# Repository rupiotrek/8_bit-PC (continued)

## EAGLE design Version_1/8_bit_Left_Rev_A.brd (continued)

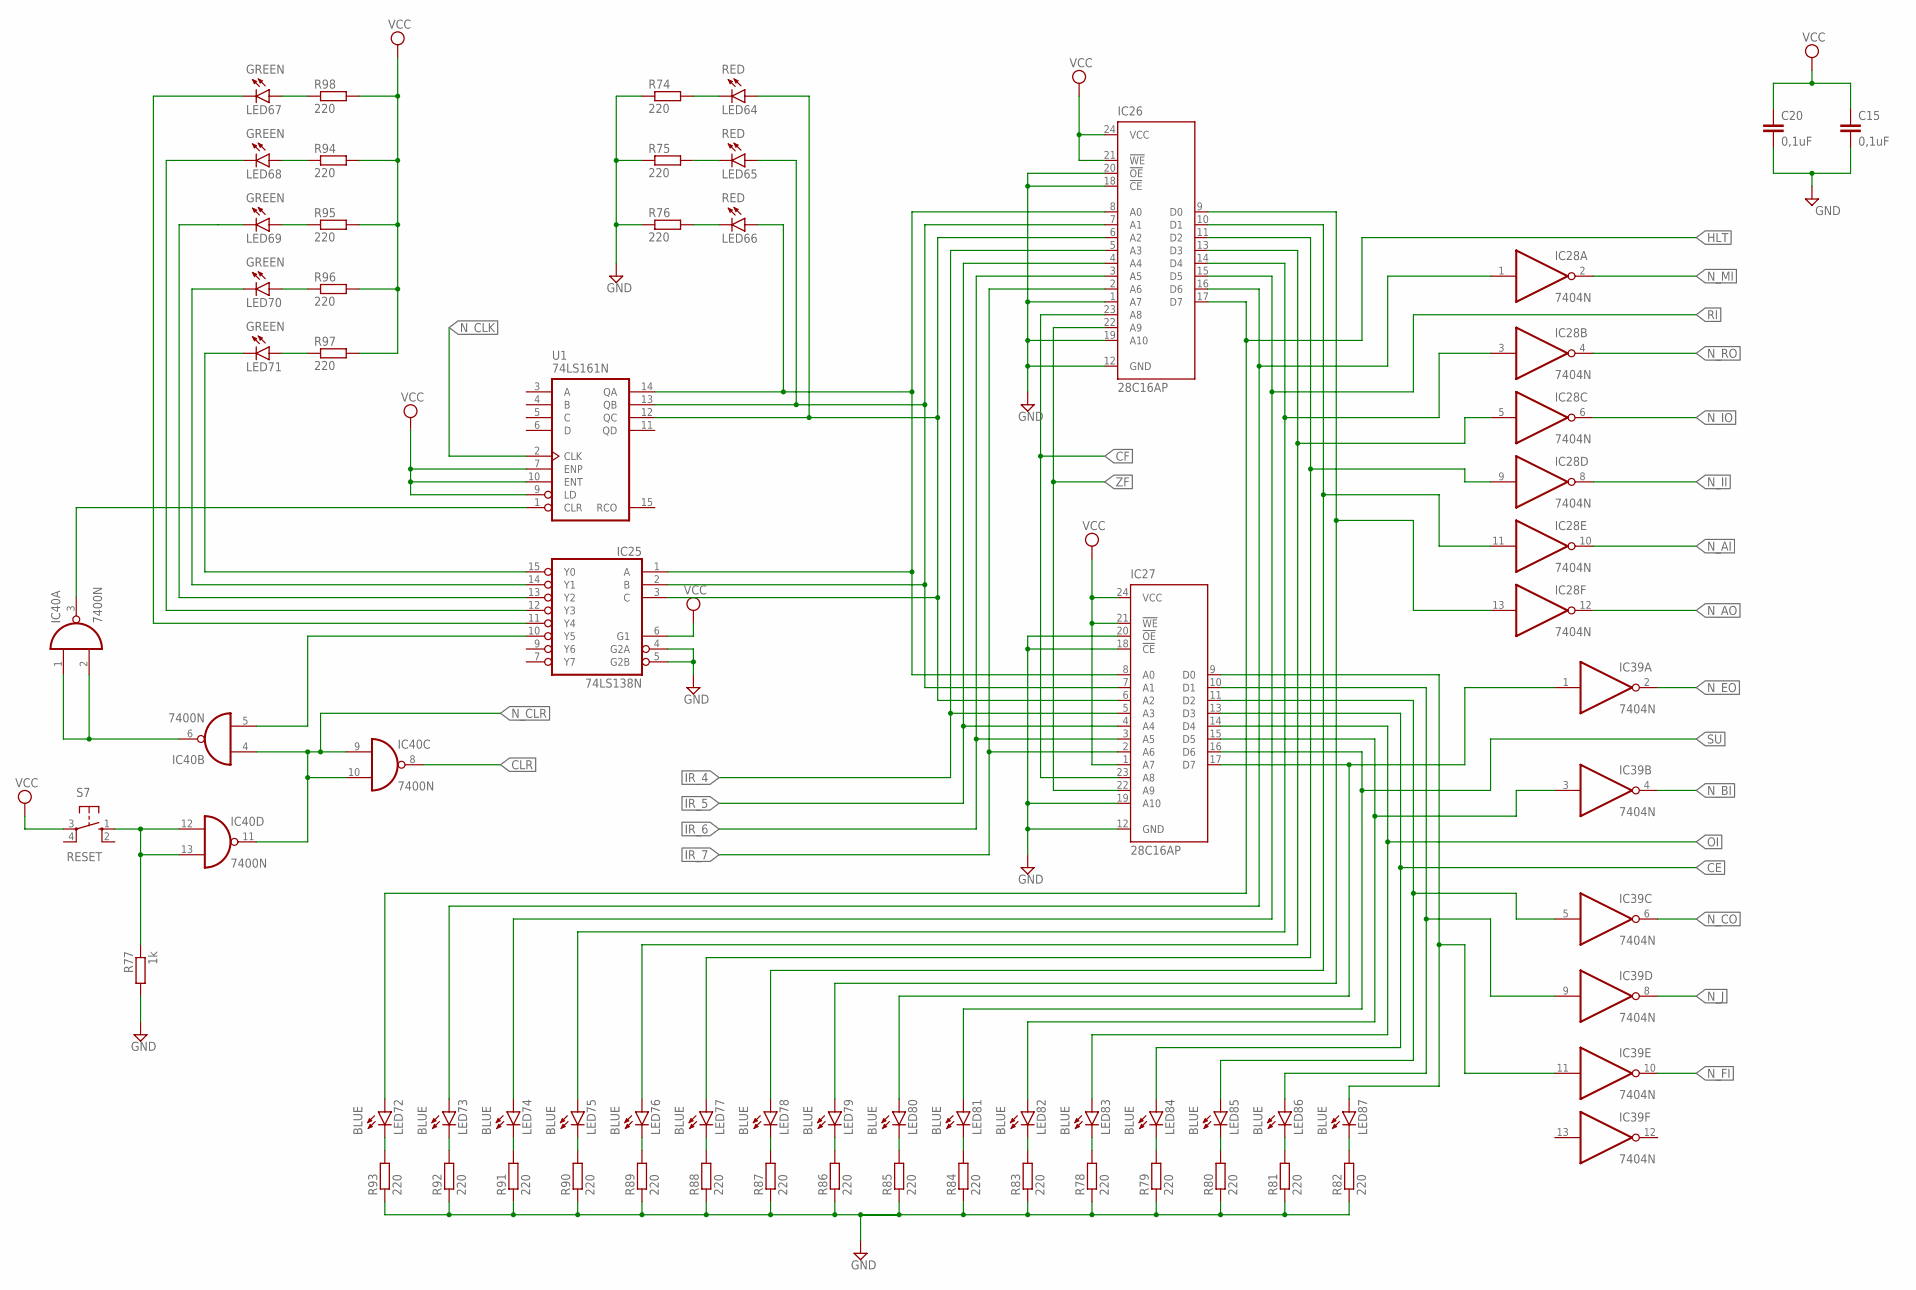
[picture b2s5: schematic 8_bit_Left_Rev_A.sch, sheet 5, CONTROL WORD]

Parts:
C15, C20: 0,1uF; C025-030X050
IC25: 74LS138N; DIL16
IC26, IC27: 28C16AP; DIL24-6
IC28, IC39: 7404N; DIL14
IC40: 7400N; DIL14
LED64, LED65, LED66: RED; LED5MM
LED67, LED68, LED69, LED70, LED71: GREEN; LED5MM
LED72, LED73, LED74, LED75, LED76, LED77, LED78, LED79, LED80, LED81, LED82, LED83, LED84, LED85, LED86, LED87: BLUE; LED5MM
R74, R75, R76, R78, R79, R80, R81, R82, R83, R84, R85, R86, R87, R88, R89, R90, R91, R92, R93, R94, R95, R96, R97, R98: 220; 0207/10
R77: 1k; 0207/10
S7: RESET; B3F-10XX
U1: 74LS161N; DIL16

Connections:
ASD1: IC25.10 (Y5), IC40.5 (I1)
CE: IC27.13 (D3), LED84.A; also elsewhere on the board
CF: IC26.23 (A8), IC27.23 (A8); also elsewhere on the board
CLK4: IC25.1 (A), IC26.8 (A0), IC27.8 (A0), LED66.A, U1.14 (QA)
CLK5: IC25.2 (B), IC26.7 (A1), IC27.7 (A1), LED65.A, U1.13 (QB)
CLK6: IC25.3 (C), IC26.6 (A2), IC27.6 (A2), LED64.A, U1.12 (QC)
CLR: IC40.8 (O); also elsewhere on the board
GND: C15.2, C20.2, IC25.4 (G2A), IC25.5 (G2B), IC25.8 (GND), IC26.1 (A7), IC26.12 (GND), IC26.18 (!CE), IC26.19 (A10), IC26.20 (!OE), IC27.12 (GND), IC27.18 (!CE), IC27.19 (A10), IC27.20 (!OE), IC28.7 (GND), IC39.7 (GND), IC40.7 (GND), R74.1, R75.1, R76.1, R77.2, R78.1, R79.1, R80.1, R81.1, R82.1, R83.1, R84.1, R85.1, R86.1, R87.1, R88.1, R89.1, R90.1, R91.1, R92.1, R93.1, U1.8 (GND); also elsewhere on the board
GND61: LED64.K (C), R74.2
GND62: LED65.K (C), R75.2
GND63: LED66.K (C), R76.2
GND64: IC25.12 (Y3), LED68.K (C)
GND65: IC25.13 (Y2), LED69.K (C)
GND66: IC25.14 (Y1), LED70.K (C)
GND67: IC25.15 (Y0), LED71.K (C)
GND68: IC25.11 (Y4), LED67.K (C)
GND69: LED83.K (C), R78.2
GND70: LED84.K (C), R79.2
GND71: LED85.K (C), R80.2
GND72: LED86.K (C), R81.2
GND73: LED87.K (C), R82.2
GND74: LED82.K (C), R83.2
GND75: LED81.K (C), R84.2
GND76: LED80.K (C), R85.2
GND77: LED79.K (C), R86.2
GND78: LED78.K (C), R87.2
GND79: LED77.K (C), R88.2
GND80: LED76.K (C), R89.2
GND81: LED75.K (C), R90.2
GND82: LED74.K (C), R91.2
GND83: LED73.K (C), R92.2
GND84: LED72.K (C), R93.2
HLT: IC26.17 (D7), LED72.A; also elsewhere on the board
IR_4: IC26.5 (A3), IC27.5 (A3); also elsewhere on the board
IR_5: IC26.4 (A4), IC27.4 (A4); also elsewhere on the board
IR_6: IC26.3 (A5), IC27.3 (A5); also elsewhere on the board
IR_7: IC26.2 (A6), IC27.2 (A6); also elsewhere on the board
unnamed: IC40.1 (I0), IC40.2 (I1), IC40.6 (O)
unnamed: IC40.3 (O), U1.1 (CLR)
unnamed: IC40.12 (I0), IC40.13 (I1), R77.1, S7.1 (S)
unnamed: IC26.14 (D4), IC28.3 (I), LED75.A
unnamed: IC26.13 (D3), IC28.5 (I), LED76.A
unnamed: IC26.11 (D2), IC28.9 (I), LED77.A
unnamed: IC26.10 (D1), IC28.11 (I), LED78.A
unnamed: IC26.9 (D0), IC28.13 (I), LED79.A
unnamed: IC27.17 (D7), IC39.1 (I), LED80.A
unnamed: IC27.15 (D5), IC39.3 (I), LED82.A
unnamed: IC27.11 (D2), IC39.5 (I), LED85.A
unnamed: IC27.10 (D1), IC39.9 (I), LED86.A
unnamed: IC27.9 (D0), IC39.11 (I), LED87.A
unnamed: LED69.A, R95.1
unnamed: LED68.A, R94.1
unnamed: LED70.A, R96.1
unnamed: LED67.A, R98.1
unnamed: LED71.A, R97.1
N_AI: IC28.10 (O); also elsewhere on the board
N_AO: IC28.12 (O); also elsewhere on the board
N_BI: IC39.4 (O); also elsewhere on the board
N_CLK: U1.2 (CLK); also elsewhere on the board
N_CLR: IC40.4 (I0), IC40.9 (I0), IC40.10 (I1), IC40.11 (O); also elsewhere on the board
N_CO: IC39.6 (O); also elsewhere on the board
N_EO: IC39.2 (O); also elsewhere on the board
N_FI: IC39.10 (O); also elsewhere on the board
N_II: IC28.8 (O); also elsewhere on the board
N_IO: IC28.6 (O); also elsewhere on the board
N_J: IC39.8 (O); also elsewhere on the board
N_MI: IC28.2 (O); also elsewhere on the board
N_RO: IC28.4 (O); also elsewhere on the board
OI: IC27.14 (D4), LED83.A; also elsewhere on the board
QWER1: IC26.16 (D6), IC28.1 (I), LED73.A
RI: IC26.15 (D5), LED74.A; also elsewhere on the board
SU: IC27.16 (D6), LED81.A; also elsewhere on the board
VCC: C15.1, C20.1, IC25.6 (G1), IC25.16 (VCC), IC26.21 (!WE), IC26.24 (VCC), IC27.1 (A7), IC27.21 (!WE), IC27.24 (VCC), IC28.14 (VCC), IC39.14 (VCC), IC40.14 (VCC), R94.2, R95.2, R96.2, R97.2, R98.2, S7.3, U1.7 (ENP), U1.9 (LD), U1.10 (ENT), U1.16 (VCC); also elsewhere on the board
ZF: IC26.22 (A9), IC27.22 (A9); also elsewhere on the board

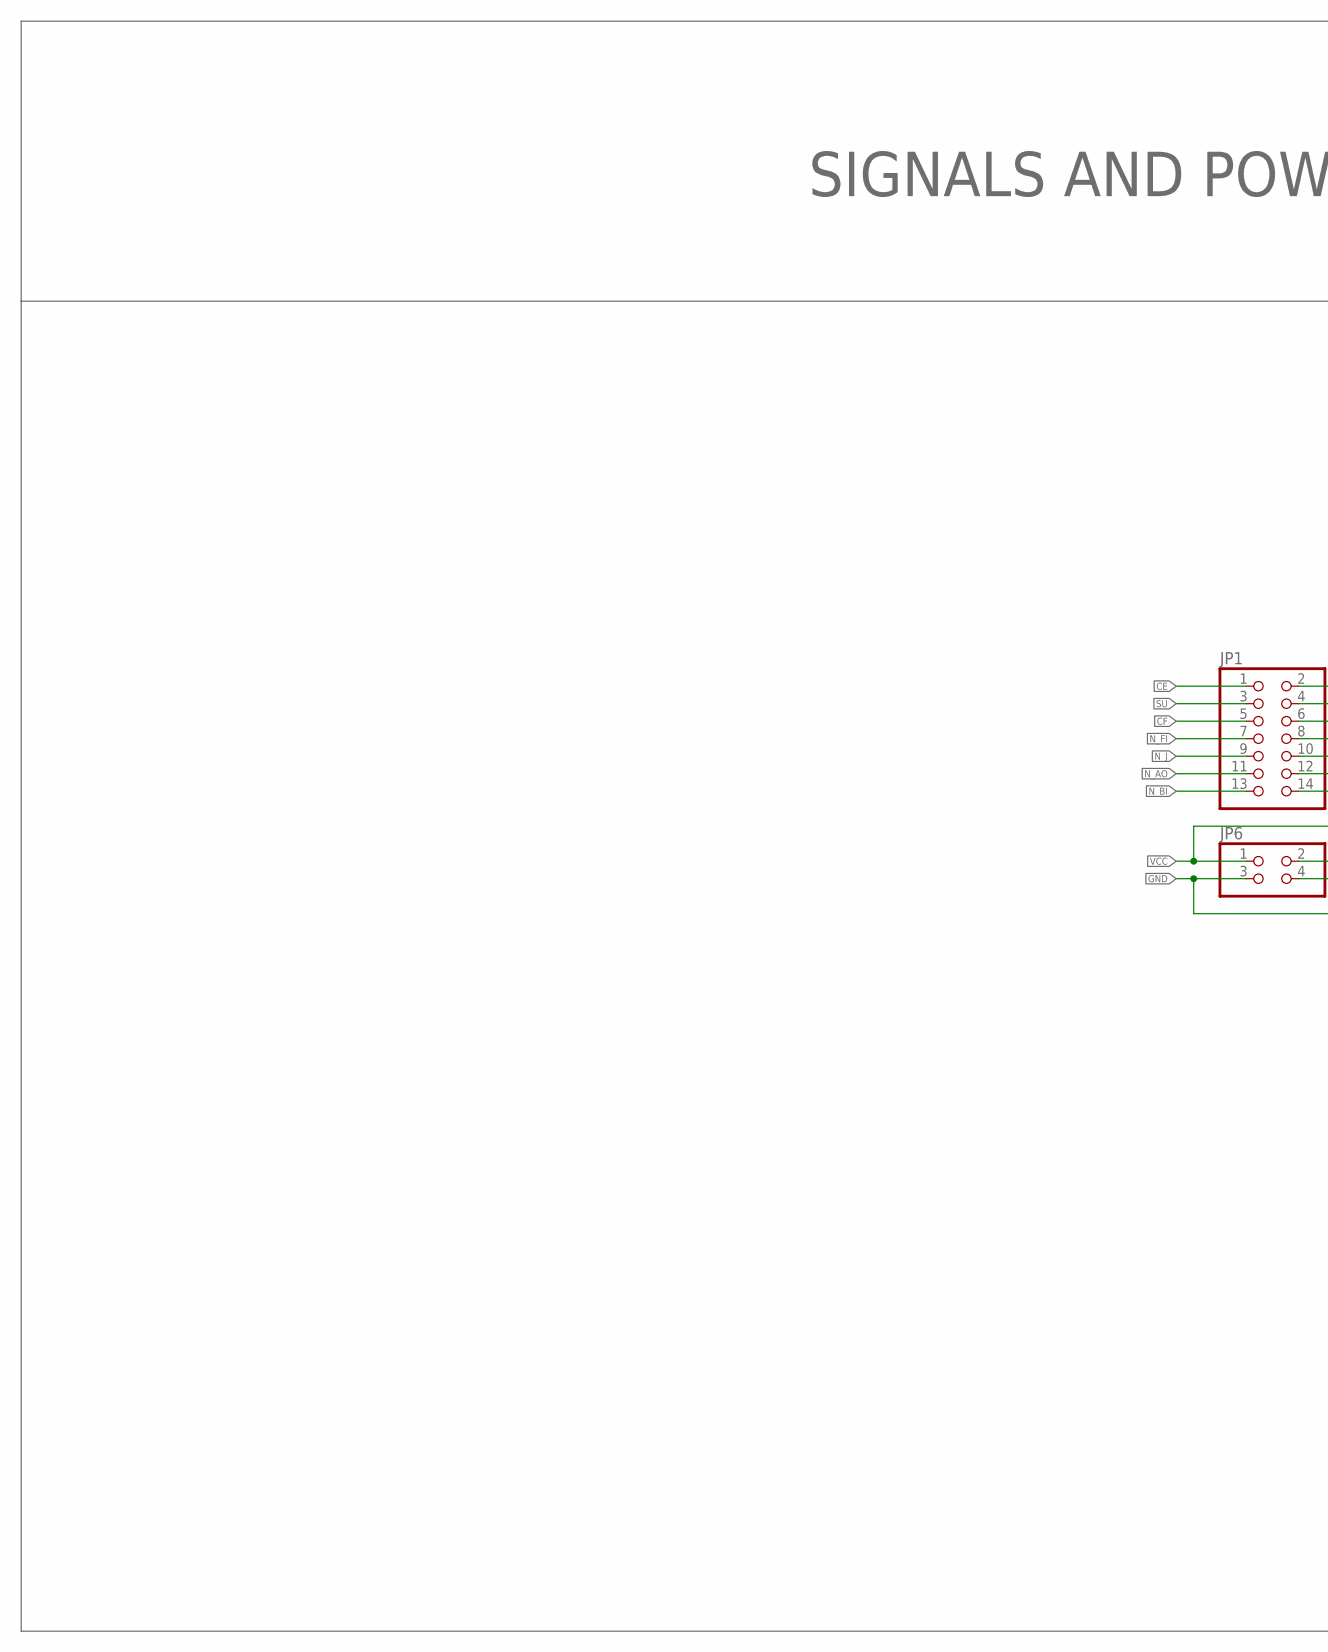
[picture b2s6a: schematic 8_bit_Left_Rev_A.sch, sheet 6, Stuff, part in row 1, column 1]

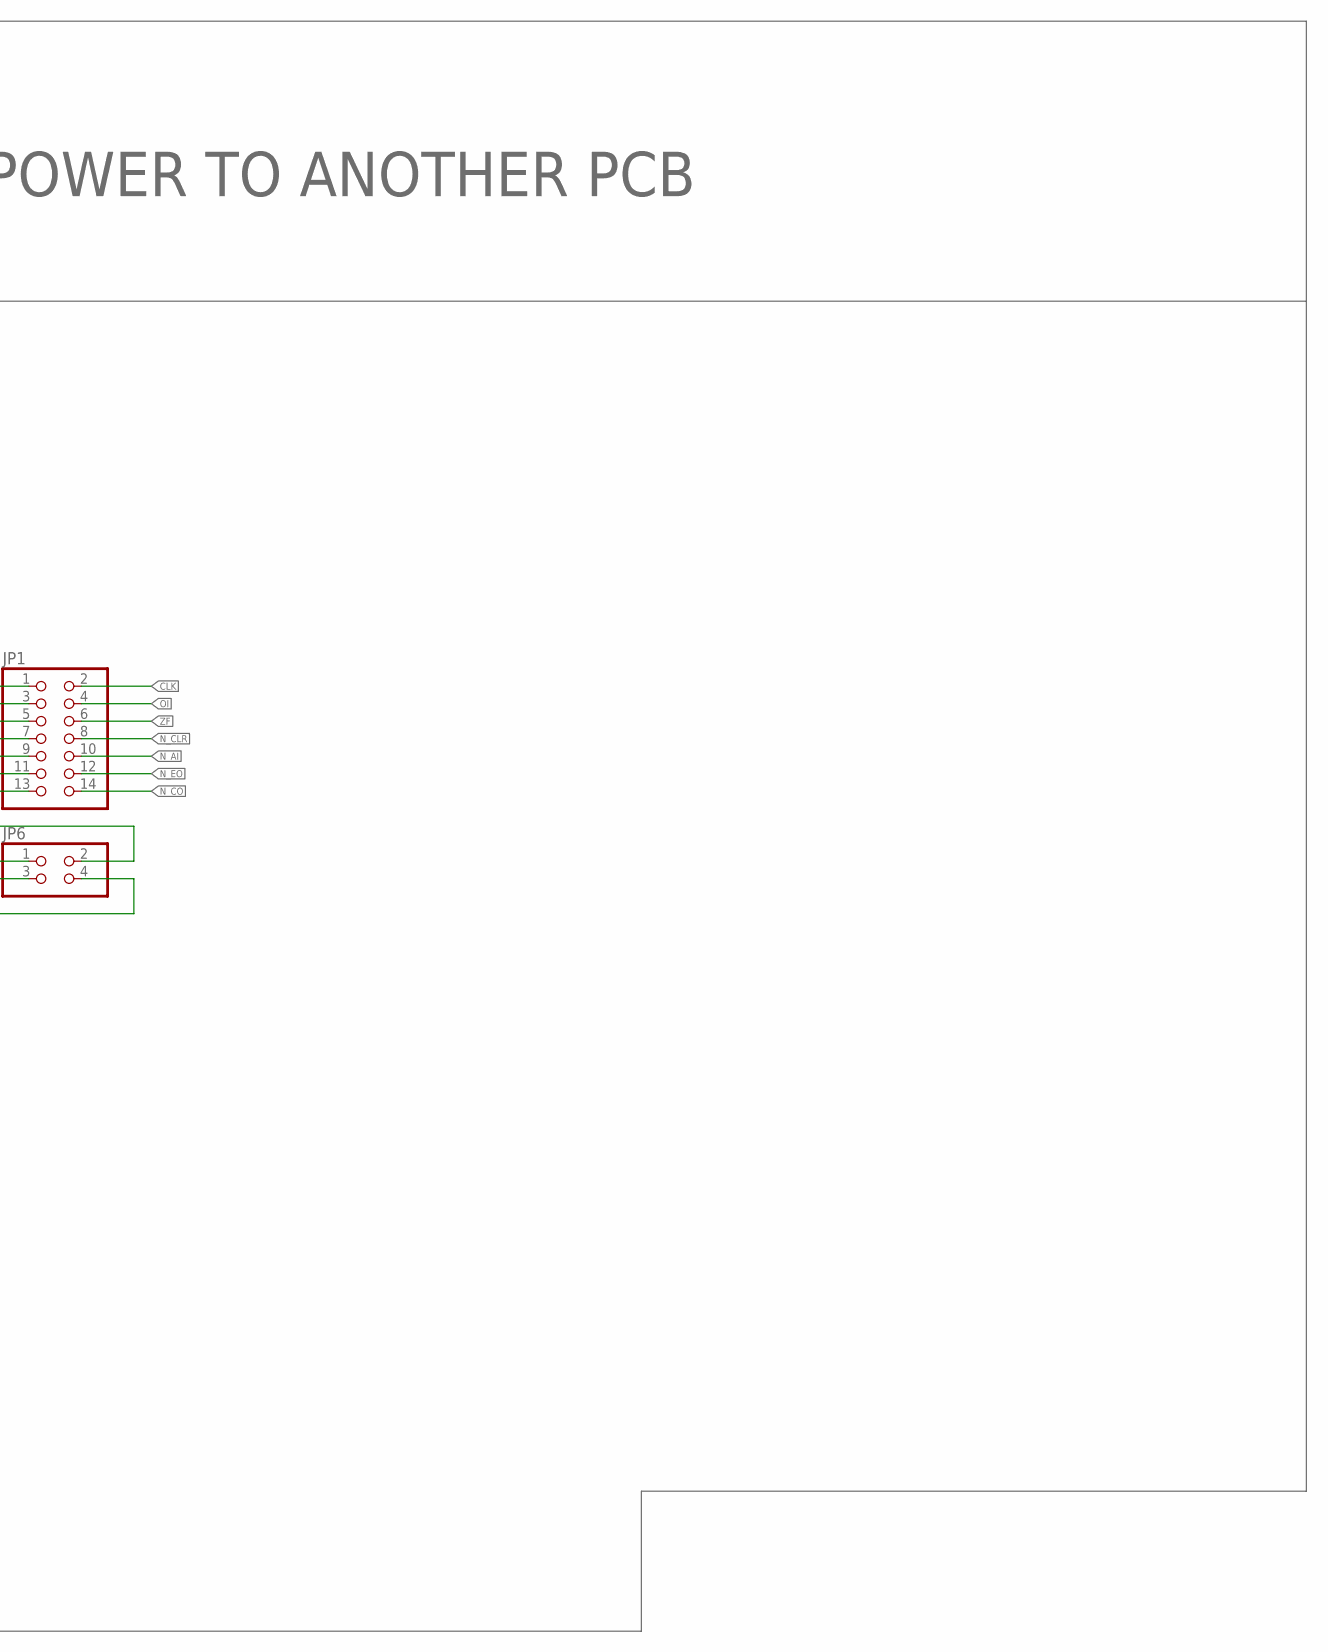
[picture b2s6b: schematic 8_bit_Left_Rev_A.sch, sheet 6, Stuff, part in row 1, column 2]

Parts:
JP1: PINHD-2X7; 2X07
JP6: PINHD-2X2; 2X02

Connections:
CE: JP1.1; also elsewhere on the board
CF: JP1.5; also elsewhere on the board
CLK: JP1.2; also elsewhere on the board
GND: JP6.3, JP6.4; also elsewhere on the board
N_AI: JP1.10; also elsewhere on the board
N_AO: JP1.11; also elsewhere on the board
N_BI: JP1.13; also elsewhere on the board
N_CLR: JP1.8; also elsewhere on the board
N_CO: JP1.14; also elsewhere on the board
N_EO: JP1.12; also elsewhere on the board
N_FI: JP1.7; also elsewhere on the board
N_J: JP1.9; also elsewhere on the board
OI: JP1.4; also elsewhere on the board
SU: JP1.3; also elsewhere on the board
VCC: JP6.1, JP6.2; also elsewhere on the board
ZF: JP1.6; also elsewhere on the board

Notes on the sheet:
SIGNALS AND POWER TO ANOTHER PCB

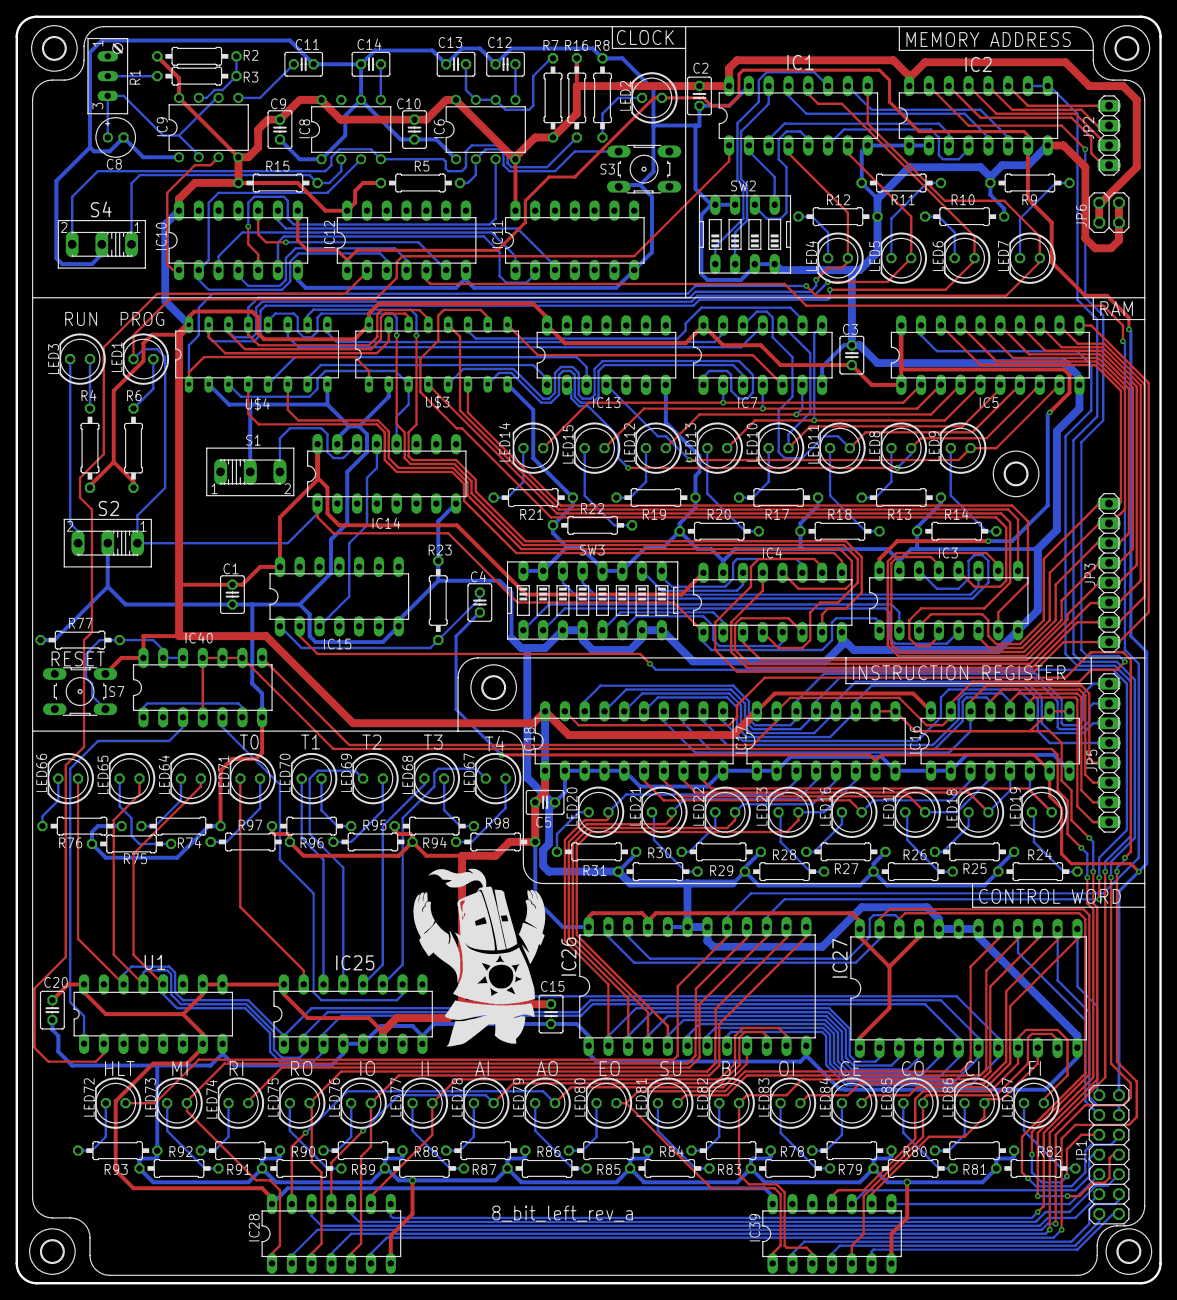
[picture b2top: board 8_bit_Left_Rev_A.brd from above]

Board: 2 copper layers, 146.8 x 162.6 mm, 164 parts (1 on the bottom side), 190 nets.

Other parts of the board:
H1, H2, H3, H4, H5, H6: MOUNT-HOLE2.8; 2,8
U$1: MUELLTONNE_10.00
U$2: SOLAIRE

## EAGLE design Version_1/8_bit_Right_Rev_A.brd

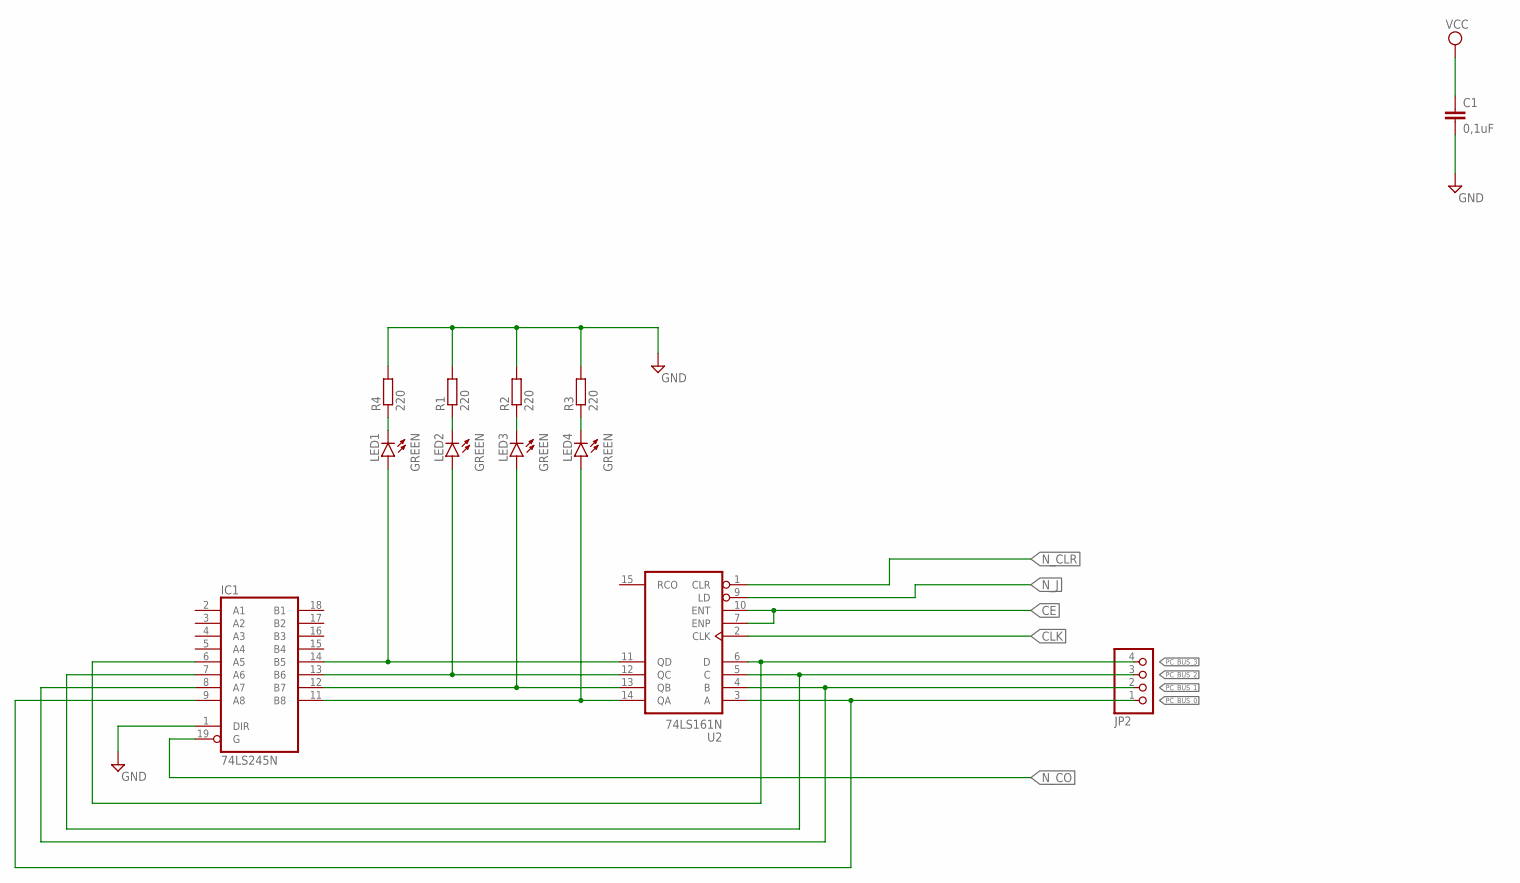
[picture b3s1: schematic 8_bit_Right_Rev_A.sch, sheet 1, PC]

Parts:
C1: 0,1uF; C025-030X050
IC1: 74LS245N; DIL20
JP2: PINHD-1X4; 1X04
LED1, LED2, LED3, LED4: GREEN; LED5MM
R1, R2, R3, R4: 220; 0207/10
U2: 74LS161N; DIL16

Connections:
CE: U2.7 (ENP), U2.10 (ENT); also elsewhere on the board
CLK: U2.2 (CLK); also elsewhere on the board
GND: C1.2, IC1.1 (DIR), IC1.10 (GND), R1.2, R2.2, R3.2, R4.2, U2.8 (GND); also elsewhere on the board
unnamed: LED1.K (C), R4.1
unnamed: LED2.K (C), R1.1
unnamed: LED3.K (C), R2.1
unnamed: LED4.K (C), R3.1
unnamed: IC1.11 (B8), LED4.A, U2.14 (QA)
unnamed: IC1.12 (B7), LED3.A, U2.13 (QB)
unnamed: IC1.13 (B6), LED2.A, U2.12 (QC)
unnamed: IC1.14 (B5), LED1.A, U2.11 (QD)
N_CLR: U2.1 (CLR); also elsewhere on the board
N_CO: IC1.19 (G); also elsewhere on the board
N_J: U2.9 (LD); also elsewhere on the board
PC_BUS_0: IC1.9 (A8), JP2.1, U2.3 (A)
PC_BUS_1: IC1.8 (A7), JP2.2, U2.4 (B)
PC_BUS_2: IC1.7 (A6), JP2.3, U2.5 (C)
PC_BUS_3: IC1.6 (A5), JP2.4, U2.6 (D)
VCC: C1.1, IC1.20 (VCC), U2.16 (VCC); also elsewhere on the board

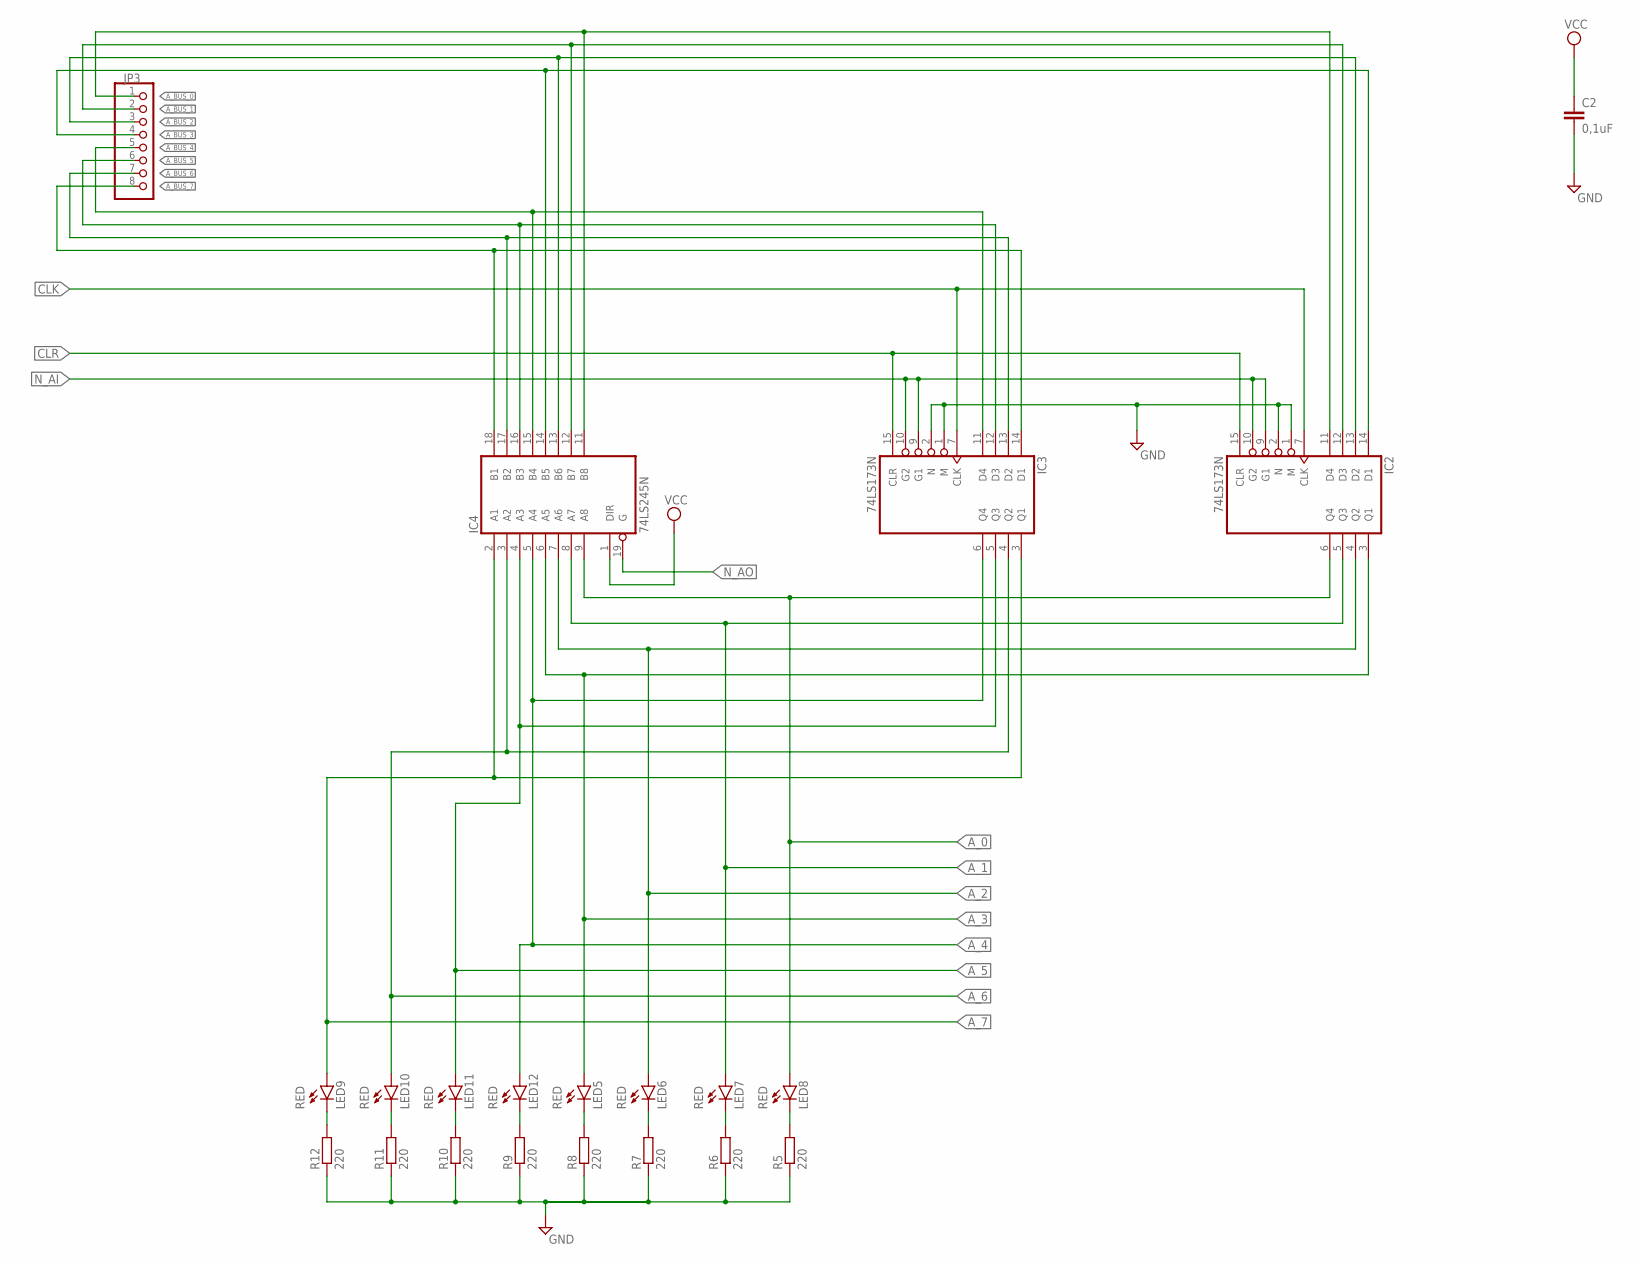
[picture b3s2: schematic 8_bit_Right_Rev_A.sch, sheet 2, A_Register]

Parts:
C2: 0,1uF; C025-030X050
IC2, IC3: 74LS173N; DIL16
IC4: 74LS245N; DIL20
JP3: PINHD-1X8; 1X08
LED5, LED6, LED7, LED8, LED9, LED10, LED11, LED12: RED; LED5MM
R5, R6, R7, R8, R9, R10, R11, R12: 220; 0207/10

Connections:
A_0: IC2.6 (Q4), IC4.9 (A8), LED8.A; also elsewhere on the board
A_1: IC2.5 (Q3), IC4.8 (A7), LED7.A; also elsewhere on the board
A_2: IC2.4 (Q2), IC4.7 (A6), LED6.A; also elsewhere on the board
A_3: IC2.3 (Q1), IC4.6 (A5), LED5.A; also elsewhere on the board
A_4: IC3.6 (Q4), IC4.5 (A4), LED12.A; also elsewhere on the board
A_5: IC3.5 (Q3), IC4.4 (A3), LED11.A; also elsewhere on the board
A_6: IC3.4 (Q2), IC4.3 (A2), LED10.A; also elsewhere on the board
A_7: IC3.3 (Q1), IC4.2 (A1), LED9.A; also elsewhere on the board
A_BUS_0: IC2.11 (D4), IC4.11 (B8), JP3.1
A_BUS_1: IC2.12 (D3), IC4.12 (B7), JP3.2
A_BUS_2: IC2.13 (D2), IC4.13 (B6), JP3.3
A_BUS_3: IC2.14 (D1), IC4.14 (B5), JP3.4
A_BUS_4: IC3.11 (D4), IC4.15 (B4), JP3.5
A_BUS_5: IC3.12 (D3), IC4.16 (B3), JP3.6
A_BUS_6: IC3.13 (D2), IC4.17 (B2), JP3.7
A_BUS_7: IC3.14 (D1), IC4.18 (B1), JP3.8
CLK: IC2.7 (CLK), IC3.7 (CLK); also elsewhere on the board
CLR: IC2.15 (CLR), IC3.15 (CLR); also elsewhere on the board
GND: C2.2, IC2.1 (M), IC2.2 (N), IC2.8 (GND), IC3.1 (M), IC3.2 (N), IC3.8 (GND), IC4.10 (GND), R5.1, R6.1, R7.1, R8.1, R9.1, R10.1, R11.1, R12.1; also elsewhere on the board
GND1: LED8.K (C), R5.2
GND2: LED7.K (C), R6.2
GND3: LED6.K (C), R7.2
GND4: LED5.K (C), R8.2
GND5: LED12.K (C), R9.2
GND6: LED11.K (C), R10.2
GND7: LED10.K (C), R11.2
GND8: LED9.K (C), R12.2
N_AI: IC2.9 (G1), IC2.10 (G2), IC3.9 (G1), IC3.10 (G2); also elsewhere on the board
N_AO: IC4.19 (G); also elsewhere on the board
VCC: C2.1, IC2.16 (VCC), IC3.16 (VCC), IC4.1 (DIR), IC4.20 (VCC); also elsewhere on the board

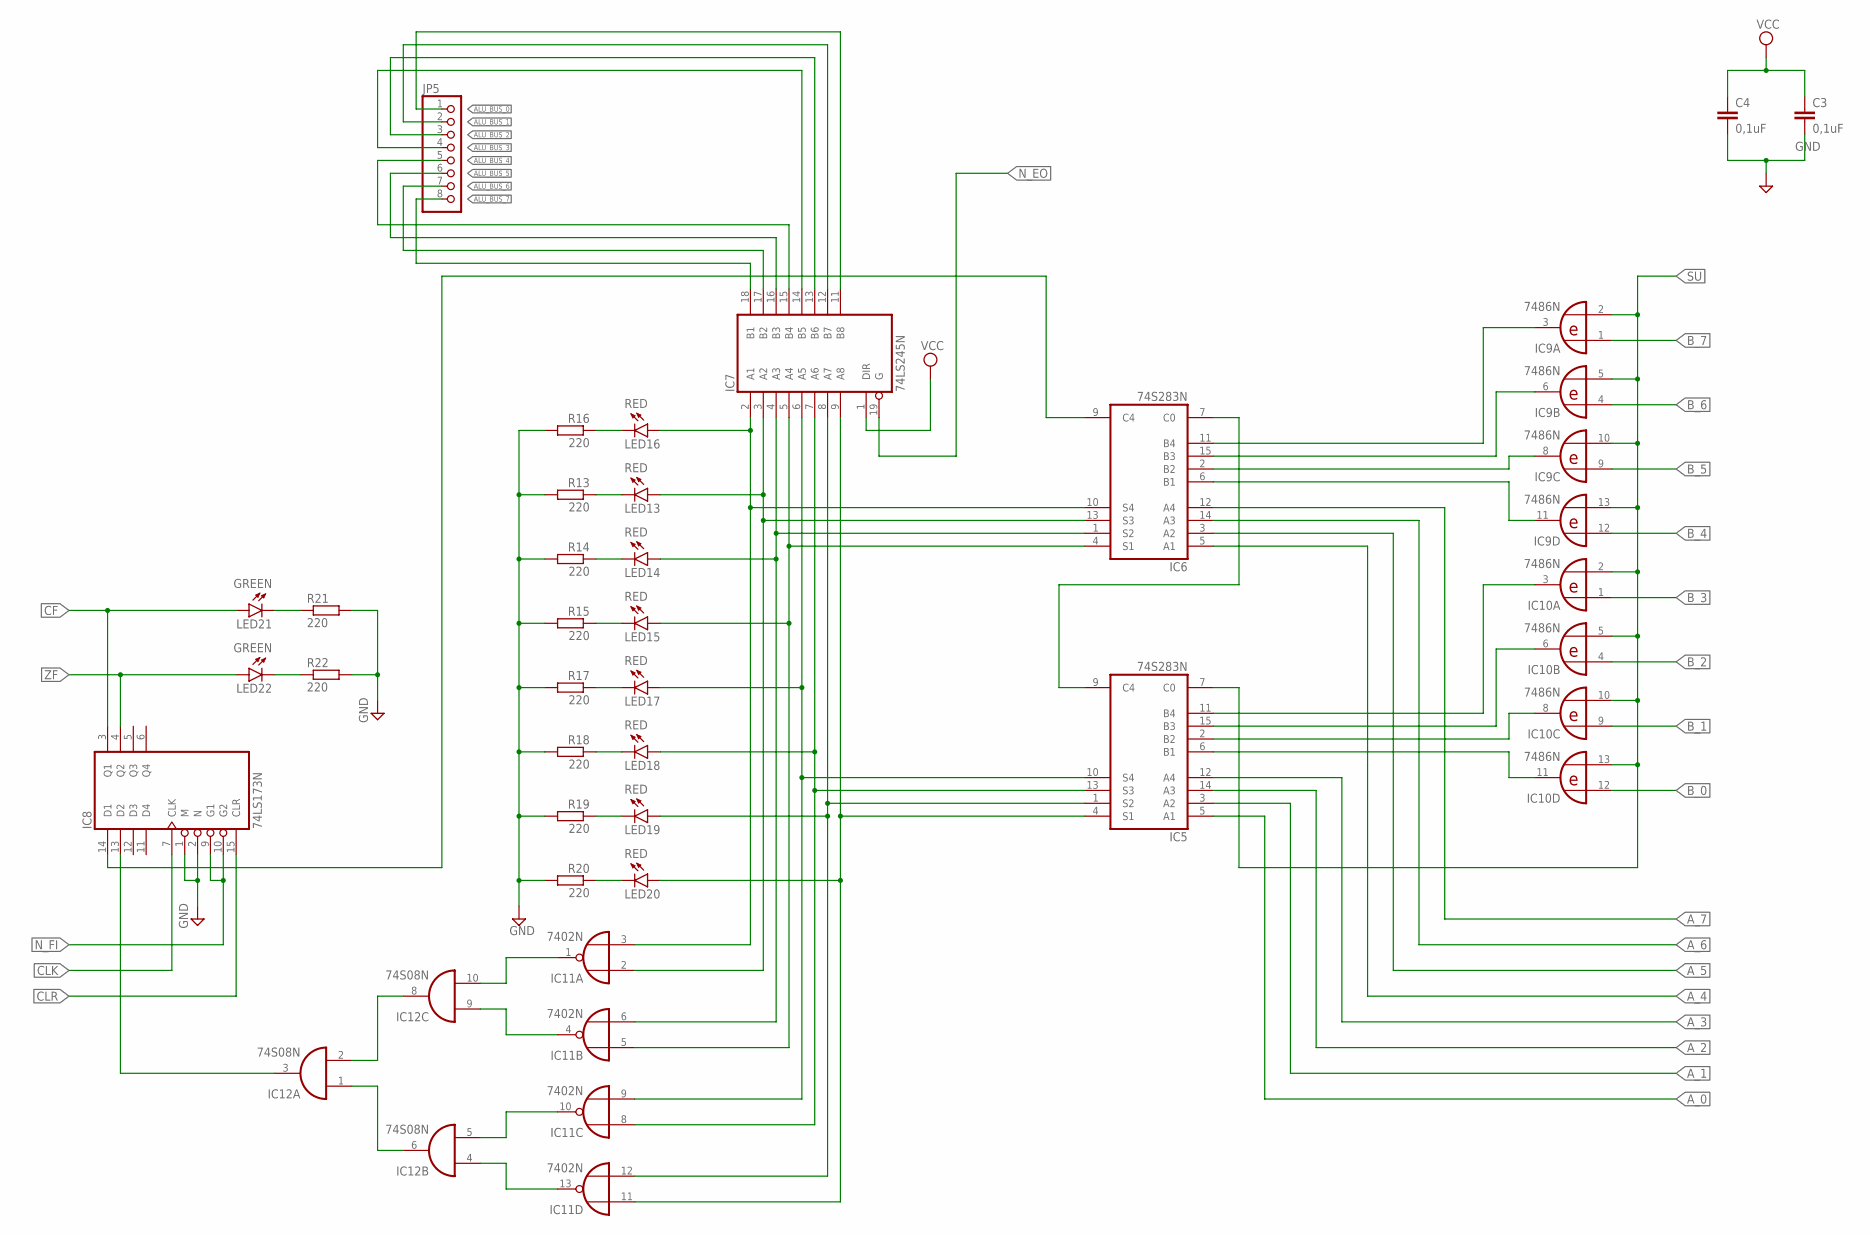
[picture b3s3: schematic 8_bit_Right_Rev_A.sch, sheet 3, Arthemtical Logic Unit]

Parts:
C3, C4: 0,1uF; C025-030X050
IC5, IC6: 74S283N; DIL16
IC7: 74LS245N; DIL20
IC8: 74LS173N; DIL16
IC9, IC10: 7486N; DIL14
IC11: 7402N; DIL14
IC12: 74S08N; DIL14
JP5: PINHD-1X8; 1X08
LED13, LED14, LED15, LED16, LED17, LED18, LED19, LED20: RED; LED5MM
LED21, LED22: GREEN; LED5MM
R13, R14, R15, R16, R17, R18, R19, R20, R21, R22: 220; 0207/10

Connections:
ALU_BUS_0: IC7.11 (B8), JP5.1
ALU_BUS_1: IC7.12 (B7), JP5.2
ALU_BUS_2: IC7.13 (B6), JP5.3
ALU_BUS_3: IC7.14 (B5), JP5.4
ALU_BUS_4: IC7.15 (B4), JP5.5
ALU_BUS_5: IC7.16 (B3), JP5.6
ALU_BUS_6: IC7.17 (B2), JP5.7
ALU_BUS_7: IC7.18 (B1), JP5.8
A_0: IC5.5 (A1); also elsewhere on the board
A_1: IC5.3 (A2); also elsewhere on the board
A_2: IC5.14 (A3); also elsewhere on the board
A_3: IC5.12 (A4); also elsewhere on the board
A_4: IC6.5 (A1); also elsewhere on the board
A_5: IC6.3 (A2); also elsewhere on the board
A_6: IC6.14 (A3); also elsewhere on the board
A_7: IC6.12 (A4); also elsewhere on the board
B_0: IC10.12 (I0); also elsewhere on the board
B_1: IC10.9 (I0); also elsewhere on the board
B_2: IC10.4 (I0); also elsewhere on the board
B_3: IC10.1 (I0); also elsewhere on the board
B_4: IC9.12 (I0); also elsewhere on the board
B_5: IC9.9 (I0); also elsewhere on the board
B_6: IC9.4 (I0); also elsewhere on the board
B_7: IC9.1 (I0); also elsewhere on the board
CF: IC8.3 (Q1), LED21.A; also elsewhere on the board
CLK: IC8.7 (CLK); also elsewhere on the board
CLR: IC8.15 (CLR); also elsewhere on the board
GND: C3.2, C4.2, IC5.8 (GND), IC6.8 (GND), IC7.10 (GND), IC8.1 (M), IC8.2 (N), IC8.8 (GND), IC9.7 (GND), IC10.7 (GND), IC11.7 (GND), IC12.7 (GND), R13.2, R14.2, R15.2, R16.2, R17.2, R18.2, R19.2, R20.2, R21.2, R22.2; also elsewhere on the board
unnamed: IC5.9 (C4), IC6.7 (C0)
unnamed: IC6.11 (B4), IC9.3 (O)
unnamed: IC6.15 (B3), IC9.6 (O)
unnamed: IC6.2 (B2), IC9.8 (O)
unnamed: IC6.6 (B1), IC9.11 (O)
unnamed: IC5.11 (B4), IC10.3 (O)
unnamed: IC5.15 (B3), IC10.6 (O)
unnamed: IC5.2 (B2), IC10.8 (O)
unnamed: IC5.6 (B1), IC10.11 (O)
unnamed: LED13.K (C), R13.1
unnamed: LED14.K (C), R14.1
unnamed: LED15.K (C), R15.1
unnamed: LED16.K (C), R16.1
unnamed: LED17.K (C), R17.1
unnamed: LED18.K (C), R18.1
unnamed: LED19.K (C), R19.1
unnamed: LED20.K (C), R20.1
unnamed: IC6.10 (S4), IC7.2 (A1), IC11.3 (I1), LED16.A
unnamed: IC6.13 (S3), IC7.3 (A2), IC11.2 (I0), LED13.A
unnamed: IC6.1 (S2), IC7.4 (A3), IC11.6 (I1), LED14.A
unnamed: IC6.4 (S1), IC7.5 (A4), IC11.5 (I0), LED15.A
unnamed: IC5.10 (S4), IC7.6 (A5), IC11.9 (I1), LED17.A
unnamed: IC5.13 (S3), IC7.7 (A6), IC11.8 (I0), LED18.A
unnamed: IC5.1 (S2), IC7.8 (A7), IC11.12 (I1), LED19.A
unnamed: IC5.4 (S1), IC7.9 (A8), IC11.11 (I0), LED20.A
unnamed: IC11.1 (O), IC12.10 (I1)
unnamed: IC11.4 (O), IC12.9 (I0)
unnamed: IC11.10 (O), IC12.5 (I1)
unnamed: IC11.13 (O), IC12.4 (I0)
unnamed: IC12.1 (I0), IC12.6 (O)
unnamed: IC12.2 (I1), IC12.8 (O)
unnamed: IC8.13 (D2), IC12.3 (O)
unnamed: IC6.9 (C4), IC8.14 (D1)
unnamed: LED21.K (C), R21.1
unnamed: LED22.K (C), R22.1
N_EO: IC7.19 (G); also elsewhere on the board
N_FI: IC8.9 (G1), IC8.10 (G2); also elsewhere on the board
SU: IC5.7 (C0), IC9.2 (I1), IC9.5 (I1), IC9.10 (I1), IC9.13 (I1), IC10.2 (I1), IC10.5 (I1), IC10.10 (I1), IC10.13 (I1); also elsewhere on the board
VCC: C3.1, C4.1, IC5.16 (VCC), IC6.16 (VCC), IC7.1 (DIR), IC7.20 (VCC), IC8.16 (VCC), IC9.14 (VCC), IC10.14 (VCC), IC11.14 (VCC), IC12.14 (VCC); also elsewhere on the board
ZF: IC8.4 (Q2), LED22.A; also elsewhere on the board
